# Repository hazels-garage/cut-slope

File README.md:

# Cut Slope

_I'm bad at pictures_

## Features
* Integrated RP2040.
* 36 key, choc-spaced, hotswap
* Ortho-ish with dropped/splayed pinkies and fanned thumbs
* Big ass screen support

## Build Guide
* Flash [Firmware](FIRMWARE.md)
* Test matrix with metal tweezers
* Install Hotswap Sockets
* Install Screen
* Done

## Credits
* [Hardware design with RP2040](https://datasheets.raspberrypi.com/rp2040/hardware-design-with-rp2040.pdf)
* [Sleepdealr's RP2040 Design Guide](https://github.com/Sleepdealr/RP2040-designguide)
* [eblastler's ZMK Design Guide](https://github.com/ebastler/zmk-designguide) - Got the SRV05-4 from here
* [Mabroum](https://github.com/AlaaSaadAbdo) - for screen suggestion and moral support
* [Sadek Baroudi](https://github.com/sadekbaroudi) - moral support
* [The Glitch Mob](https://www.youtube.com/watch?v=HD7XAOhkd-w) - for the name

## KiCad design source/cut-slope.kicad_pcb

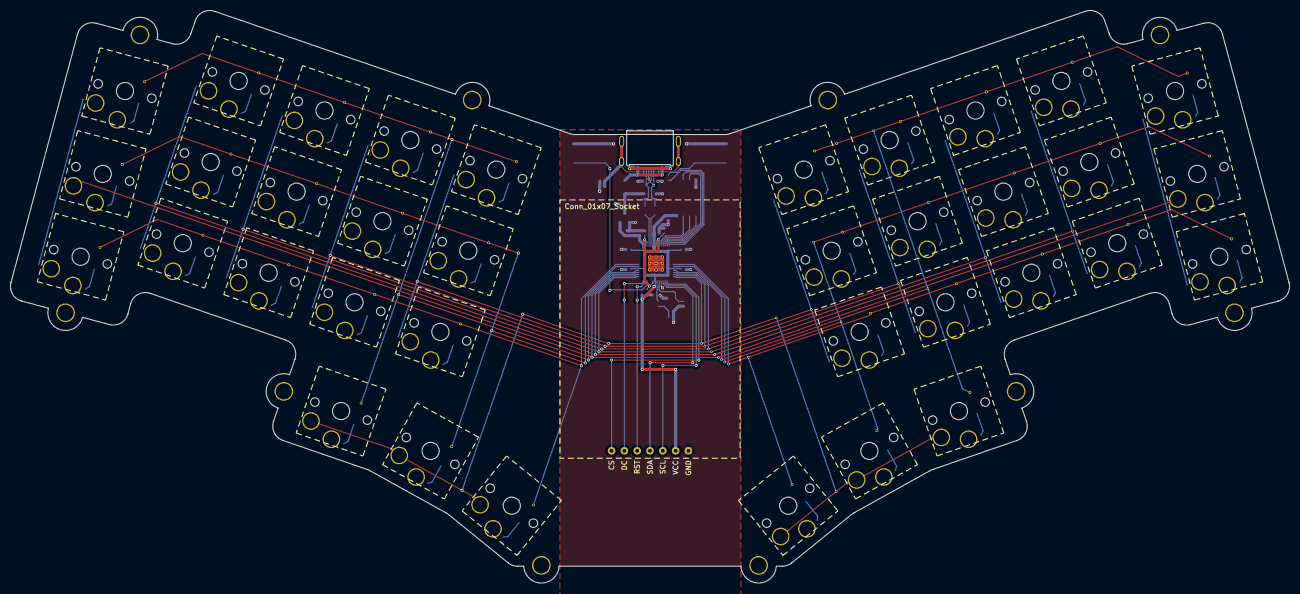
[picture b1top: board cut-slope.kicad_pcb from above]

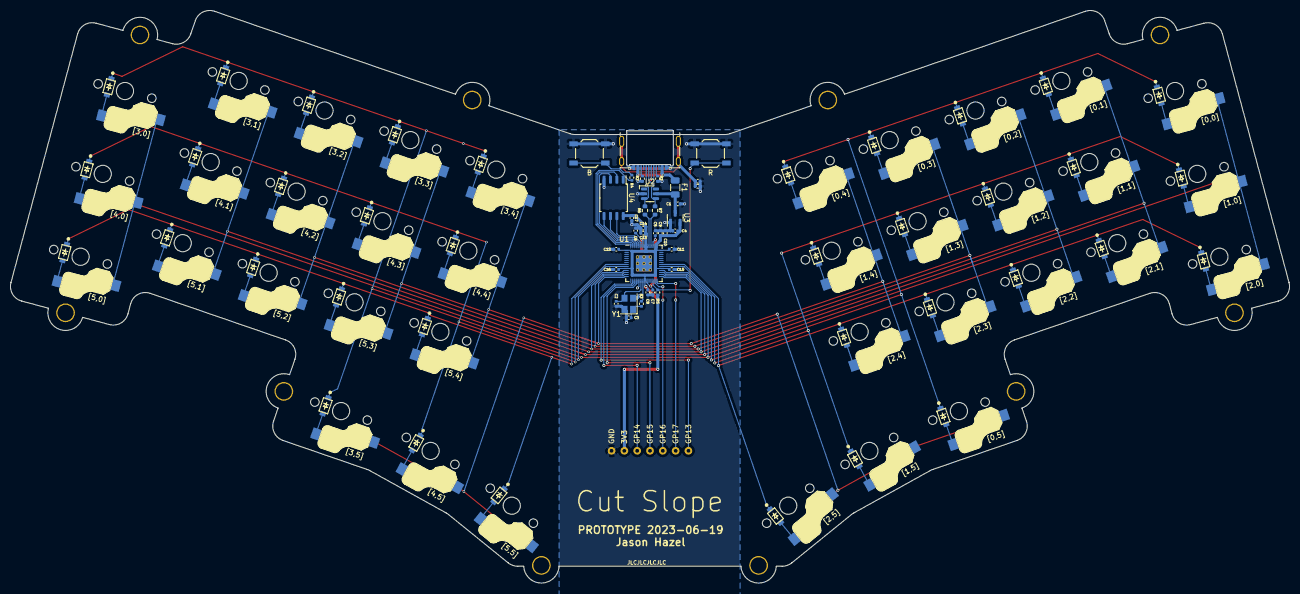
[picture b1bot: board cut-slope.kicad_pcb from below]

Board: 2 copper layers, 253.5 x 113.5 mm, 119 parts (71 on the bottom side), 76 nets.

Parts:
BOOT1: B; SW_SPST_TL3342
C1, C4, C5: 1uF; C_0402_1005Metric
C2, C3: 22pF; C_0402_1005Metric
C6, C7, C8, C9, C10, C11, C12, C13, C14, C15, C16, C17: 100nF; C_0402_1005Metric
C_Shield1: 4.7n; C_0402_1005Metric
D1, D2, D3, D4, D5, D6, D7, D8, D9, D10, D11, D12, D13, D14, D15, D16, D17, D18, D19, D20, D21, D22, D23, D24, D25, D26, D27, D28, D29, D30, D31, D32, D33, D34, D35, D36: 1N4148W; D_SOD-123
F1: 500mA; Fuse_1206_3216Metric
H1, H2, H3, H4, H5, H6, H7, H8, H9, H10: MountingHole; MountingHole_3.2mm_M3_thinpad
J1: USB_C; Molex-216990_GCT-USB45xx_HRO-TYPE-C-31-M-13x
J2: Conn_01x07_Socket; big ass screen
JLC1: JLCJLCJLCJLC
R1, R2: 5.1k; R_0402_1005Metric
R3, R4: 1k; R_0402_1005Metric
R5: 10k; R_0402_1005Metric
R6, R7: 27R; R_0603_1608Metric
RESET1: R; SW_SPST_TL3342
R_Shield1: 1M; R_0402_1005Metric
SW1: [2,0]; Choc-1u
SW2: [1,0]; Choc-1u
SW3: [0,0]; Choc-1u
SW4: [2,1]; Choc-1u
SW5: [1,1]; Choc-1u
SW6: [0,1]; Choc-1u
SW7: [2,2]; Choc-1u
SW8: [1,2]; Choc-1u
SW9: [0,2]; Choc-1u
SW10: [2,3]; Choc-1u
SW11: [1,3]; Choc-1u
SW12: [0,3]; Choc-1u
SW13: [2,4]; Choc-1u
SW14: [1,4]; Choc-1u
SW15: [0,4]; Choc-1u
SW16: [0,5]; Choc-1u
SW17: [1,5]; Choc-1u
SW18: [2,5]; Choc-1u
SW19: [5,0]; Choc-1u
SW20: [4,0]; Choc-1u
SW21: [3,0]; Choc-1u
SW22: [5,1]; Choc-1u
SW23: [4,1]; Choc-1u
SW24: [3,1]; Choc-1u
SW25: [5,2]; Choc-1u
SW26: [4,2]; Choc-1u
SW27: [3,2]; Choc-1u
SW28: [5,3]; Choc-1u
SW29: [4,3]; Choc-1u
SW30: [3,3]; Choc-1u
SW31: [5,4]; Choc-1u
SW32: [4,4]; Choc-1u
SW33: [3,4]; Choc-1u
SW34: [3,5]; Choc-1u
SW35: [4,5]; Choc-1u
SW36: [5,5]; Choc-1u
U1: RP2040; RP2040-QFN-56
U2: SRV05-4; SOT-23-6-routable
U3: XC6206; SOT-23
U4: W25Q128JVS; SOIC-8_5.23x5.23mm_P1.27mm
Y1: 12MHz; Crystal_SMD_3225-4Pin_3.2x2.5mm

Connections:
+1V1: C5.1, C6.1, C7.1, U1.23 (DVDD), U1.45 (VREG_VOUT), U1.50 (DVDD)
+3V3: C4.2, C8.1, C9.1, C10.1, C11.1, C12.1, C13.1, C14.1, C15.1, C16.1, C17.1, J2.2, R5.1, U1.1 (IOVDD), U1.10 (IOVDD), U1.22 (IOVDD), U1.33 (IOVDD), U1.42 (IOVDD), U1.43 (ADC_AVDD), U1.44 (VREG_VIN), U1.48 (USB_VDD), U1.49 (IOVDD), U3.2 (VO), U4.8 (VCC)
+5V: C1.2, F1.2, U2.5 (VP), U3.3 (VI)
/DC: J2.6, U1.28 (GPIO17)
/RST: J2.5, U1.27 (GPIO16)
/SPI1_CS: J2.7, U1.16 (GPIO13)
/SPI1_MOSI: J2.4, U1.18 (GPIO15)
/SPI1_SCK: J2.3, U1.17 (GPIO14)
/col0: SW1.1, SW2.1, SW3.1, SW19.1, SW20.1, SW21.1, U1.31 (GPIO20)
/col1: SW4.1, SW5.1, SW6.1, SW22.1, SW23.1, SW24.1, U1.30 (GPIO19)
/col2: SW7.1, SW8.1, SW9.1, SW25.1, SW26.1, SW27.1, U1.29 (GPIO18)
/col3: SW10.1, SW11.1, SW12.1, SW28.1, SW29.1, SW30.1, U1.12 (GPIO9)
/col4: SW13.1, SW14.1, SW15.1, SW31.1, SW32.1, SW33.1, U1.13 (GPIO10)
/col5: SW16.1, SW17.1, SW18.1, SW34.1, SW35.1, SW36.1, U1.14 (GPIO11)
/row0: D3.1 (K), D6.1 (K), D9.1 (K), D12.1 (K), D15.1 (K), D16.1 (K), U1.32 (GPIO21)
/row1: D2.1 (K), D5.1 (K), D8.1 (K), D11.1 (K), D14.1 (K), D17.1 (K), U1.34 (GPIO22)
/row2: D1.1 (K), D4.1 (K), D7.1 (K), D10.1 (K), D13.1 (K), D18.1 (K), U1.35 (GPIO23)
/row3: D21.1 (K), D24.1 (K), D27.1 (K), D30.1 (K), D33.1 (K), D34.1 (K), U1.11 (GPIO8)
/row4: D20.1 (K), D23.1 (K), D26.1 (K), D29.1 (K), D32.1 (K), D35.1 (K), U1.9 (GPIO7)
/row5: D19.1 (K), D22.1 (K), D25.1 (K), D28.1 (K), D31.1 (K), D36.1 (K), U1.8 (GPIO6)
/rp2040/CC1: J1.A5 (CC1), R1.1
/rp2040/CC2: J1.B5 (CC2), R2.1
/rp2040/D_+: R6.2, U1.47 (D+)
/rp2040/D_-: R7.2, U1.46 (D-)
/rp2040/XTAL_O: C3.2, R3.1, Y1.1
/rp2040/~USB_BOOT: BOOT1.1, R4.1
CS: R4.2, U1.56 (QSPI_SS_N), U4.1 (~CS)
DBUS+: J1.A6 (D+), J1.B6 (D+), R6.1, U2.3 (IO2)
DBUS-: J1.A7 (D-), J1.B7 (D-), R7.1, U2.4 (IO3)
GND: BOOT1.2, C1.1, C2.1, C3.1, C4.1, C5.2, C6.2, C7.2, C8.2, C9.2, C10.2, C11.2, C12.2, C13.2, C14.2, C15.2, C16.2, C17.2, C_Shield1.1, J1.A1 (GND), J1.A12 (GND), J1.B1 (GND), J1.B12 (GND), J2.1, R1.2, R2.2, RESET1.2, R_Shield1.2, U1.19 (TESTEN), U1.57 (GND), U2.2 (VN), U3.1 (GND), U4.4 (GND), Y1.2, Y1.4
GNDREF: C_Shield1.2, J1.S1 (SHIELD), R_Shield1.1
unnamed: D1.2 (A), SW1.2
unnamed: D2.2 (A), SW2.2
unnamed: D3.2 (A), SW3.2
unnamed: D4.2 (A), SW4.2
unnamed: D5.2 (A), SW5.2
unnamed: D6.2 (A), SW6.2
unnamed: D7.2 (A), SW7.2
unnamed: D8.2 (A), SW8.2
unnamed: D9.2 (A), SW9.2
unnamed: D10.2 (A), SW10.2
unnamed: D11.2 (A), SW11.2
unnamed: D12.2 (A), SW12.2
unnamed: D13.2 (A), SW13.2
unnamed: D14.2 (A), SW14.2
unnamed: D15.2 (A), SW15.2
unnamed: D16.2 (A), SW16.2
unnamed: D17.2 (A), SW17.2
unnamed: D18.2 (A), SW18.2
unnamed: D19.2 (A), SW19.2
unnamed: D20.2 (A), SW20.2
unnamed: D21.2 (A), SW21.2
unnamed: D22.2 (A), SW22.2
unnamed: D23.2 (A), SW23.2
unnamed: D24.2 (A), SW24.2
unnamed: D25.2 (A), SW25.2
unnamed: D26.2 (A), SW26.2
unnamed: D27.2 (A), SW27.2
unnamed: D28.2 (A), SW28.2
unnamed: D29.2 (A), SW29.2
unnamed: D30.2 (A), SW30.2
unnamed: D31.2 (A), SW31.2
unnamed: D32.2 (A), SW32.2
unnamed: D33.2 (A), SW33.2
unnamed: D34.2 (A), SW34.2
unnamed: D35.2 (A), SW35.2
unnamed: D36.2 (A), SW36.2
QSPI_CLK: U1.52 (QSPI_SCLK), U4.6 (CLK)
SD0: U1.53 (QSPI_SD0), U4.5 (DI(IO0))
SD1: U1.55 (QSPI_SD1), U4.2 (DO(IO1))
SD2: U1.54 (QSPI_SD2), U4.3 (IO2)
SD3: U1.51 (QSPI_SD3), U4.7 (IO3)
VBUS: F1.1, J1.A4 (VBUS), J1.A9 (VBUS), J1.B4 (VBUS), J1.B9 (VBUS)
XTAL_IN: C2.2, U1.20 (XTAL_IN), Y1.3
XTAL_OUT: R3.2, U1.21 (XTAL_OUT)
~RESET: R5.2, RESET1.1, U1.26 (~RUN)

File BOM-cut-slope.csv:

Comment,Designator,Footprint,LCSC
B,"BOOT1,RESET1",SW_SPST_TL3342,C115351
1k,"R3,R4",R_0402_1005Metric,C11702
100nF,"C10,C11,C12,C13,C14,C15,C16,C17,C6,C7,C8,C9",C_0402_1005Metric,C1525
4.7n,C_Shield1,C_0402_1005Metric,C1538
22pF,"C2,C3",C_0402_1005Metric,C1555
RP2040,U1,RP2040-QFN-56,C2040
USB_C,J1,Molex-216990_GCT-USB45xx_HRO-TYPE-C-31-M-13x,C223906
27R,"R6,R7",R_0603_1608Metric,C25190
10k,R5,R_0402_1005Metric,C25744
5.1k,"R1,R2",R_0402_1005Metric,C25905
1M,R_Shield1,R_0402_1005Metric,C26083
1uF,"C1,C4,C5",C_0402_1005Metric,C52923
XC6206,U3,SOT-23,C5446
500mA,F1,Fuse_1206_3216Metric,C70076
1N4148W,"D1,D10,D11,D12,D13,D14,D15,D16,D17,D18,D19,D2,D20,D21,D22,D23,D24,D25,D26,D27,D28,D29,D3,D30,D31,D32,D33,D34,D35,D36,D4,D5,D6,D7,D8,D9",D_SOD-123,C81598
SRV05-4,U2,SOT-23-6-routable,C85364
12MHz,Y1,Crystal_SMD_3225-4Pin_3.2x2.5mm,C9002
W25Q128JVS,U4,SOIC-8_5.23x5.23mm_P1.27mm,C97521

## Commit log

2023-07-01 init
2023-07-01 readme
2023-07-01 cc-by-sa
2023-07-01 adding tray case
2023-07-01 cc-by-nc-sa
2023-07-01 add firmware
2023-08-22 some source code maybe?
2023-08-22 remove random shit
2023-08-22 fix image name
2023-08-22 whoops, missing image
2023-08-22 move image to correct directory, it's too early
2023-08-22 image caption
2023-08-22 add shout outs
2023-11-16 adding vial firmware
2023-12-05 add step
2023-12-05 how'd my dumbass miss a chamfer on one of the bottom mounting holes?
2026-03-26 Remove Hazel's Garage badge from README
    Removed badge link for Hazel's Garage from README.

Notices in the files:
README.md:
https://img.shields.io/badge/CC--BY--NC-test?style=flat-square&logo=creativecommons&logoColor=ffffff&label=%20&labelColor=8CBA04&color=8CBA04
